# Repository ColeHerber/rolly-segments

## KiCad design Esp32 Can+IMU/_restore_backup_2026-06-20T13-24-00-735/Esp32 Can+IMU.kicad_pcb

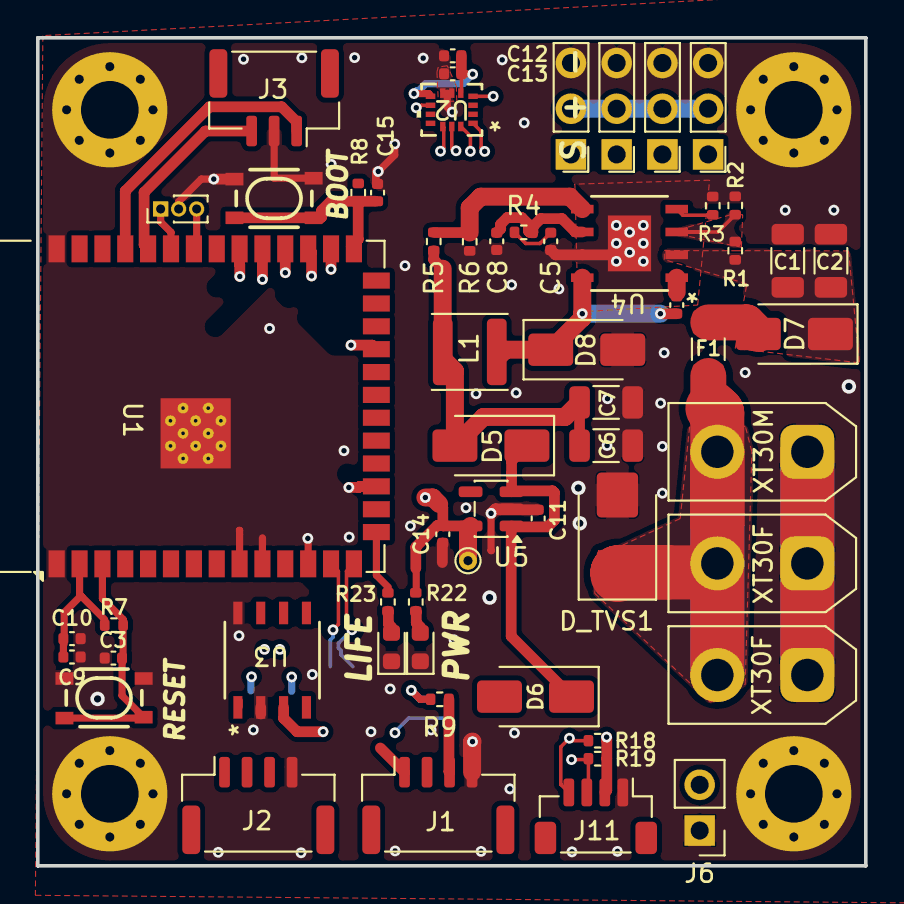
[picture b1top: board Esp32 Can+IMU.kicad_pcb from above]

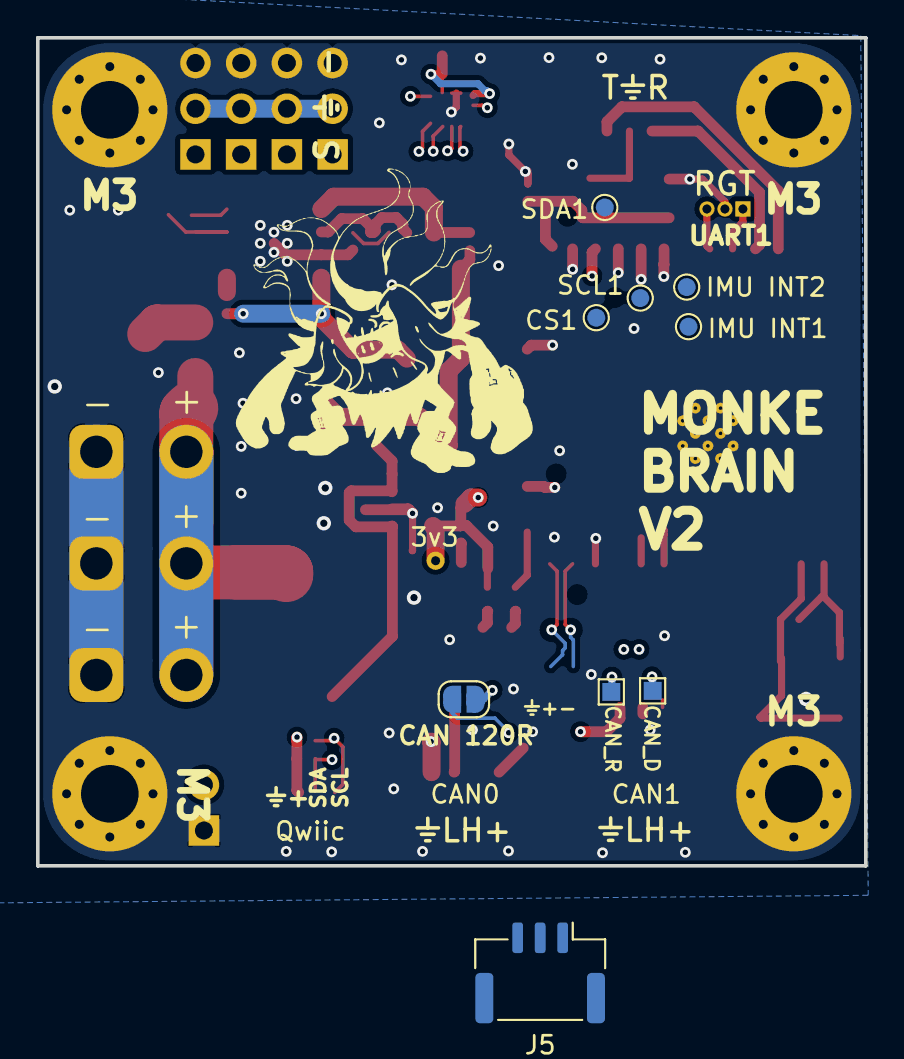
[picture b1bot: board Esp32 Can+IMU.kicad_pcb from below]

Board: 4 copper layers, 46.0 x 46.0 mm, 71 parts (10 on the bottom side), 39 nets.

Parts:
Boot2: BOOT; Push_SMD_4.2x3.2mm
C1, C2: 2.2uF 100v; C_1206_3216Metric
C3, C4, C9, C12, C13, C15: 100nF; C_0402_1005Metric
C5: 6.8nF; C_0402_1005Metric
C6, C7: 47uF 10v; C_1206_3216Metric
C8: 39pF; C_0402_1005Metric
C10: 22uF; C_0402_1005Metric
C11: 1uF 10V X5R; C_0402_1005Metric
C14: 4.7uF 10V X5R; C_0402_1005Metric
CAND1: CAN_D; TestPoint_Pad_1.0x1.0mm
CANR1: CAN_R; TestPoint_Pad_1.0x1.0mm
CAN_TERM1: CAN 120R; SolderJumper-2_P1.3mm_Open_RoundedPad1.0x1.5mm
D3: PWR; LED_0603_1608Metric
D4: LIFE; LED_0603_1608Metric
D5, D6: SS54; D_SMA
D7, D8: SS56; D_SMA
D_TVS1: SMBJ58A; D_SMB
F1: C41367225; Fuse_1206_3216Metric_Pad1.42x1.75mm_HandSolder
H1, H2, H3, H4: M3; MountingHole_3.2mm_M3_Pad_Via
J1: CAN0; JST_GH_SM04B-GHS-TB_1x04-1MP_P1.25mm_Horizontal
J2: CAN1; JST_GH_SM04B-GHS-TB_1x04-1MP_P1.25mm_Horizontal
J3: UART0; JST_GH_SM03B-GHS-TB_1x03-1MP_P1.25mm_Horizontal
J4: UART1; PinHeader_1x03_P1.00mm_Vertical
J5: USB; JST_GH_BM03B-GHS-TBT_1x03-1MP_P1.25mm_Vertical
J6: 5V PWR; PinHeader_1x02_P2.54mm_Vertical
J7: PWM1; PinHeader_1x03_P2.54mm_Vertical_Close
J8: PWM2; PinHeader_1x03_P2.54mm_Vertical_Close
J9: PWM3; PinHeader_1x03_P2.54mm_Vertical_Close
J10: PWM4; PinHeader_1x03_P2.54mm_Vertical_Close
J11: Qwiic; JST_SH_BM04B-SRSS-TB_1x04-1MP_P1.00mm_Vertical
L1: 8.2uH; L_Changjiang_FNR4010S
R1: 523k; R_0402_1005Metric
R2: 84.5kΩ; R_0402_1005Metric
R3: 162kΩ; R_0402_1005Metric
R4: 13.0kΩ; R_0402_1005Metric
R5: 59kΩ; R_0402_1005Metric
R6: 10.2kΩ; R_0402_1005Metric
R7, R8: 10k; R_0402_1005Metric
R9: 120Ω; R_0402_1005Metric
R18, R19: 4.7kΩ; R_0402_1005Metric
R22: 1k; R_0402_1005Metric
R23: 100Ω; R_0402_1005Metric
Reset1: RESET; Push_SMD_4.2x3.2mm
TP_3v3: 3v3; TestPoint_THTPad_D1.0mm_Drill0.5mm
TP_CS1: CS1; TestPoint_Pad_D1.0mm
TP_INT1: IMU INT1; TestPoint_Pad_D1.0mm
TP_INT2: IMU INT2; TestPoint_Pad_D1.0mm
TP_SCL1: SCL1; TestPoint_Pad_D1.0mm
TP_SDA1: SDA1; TestPoint_Pad_D1.0mm
U1: ESP32-S3-WROOM-1
U2: ISM6HG256XTR; LGA14L_2P5X3_STM
U3: SN65HVD230DR; D8-L
U4: TPS54360BQDDARQ1; DDA8_3P1X2P4_TEX-L
U5: AP2112K-3.3; SOT-23-5
XT30F1, XT30F2: XT30F; AMASS_XT30UPB-F_1x02_P5.0mm_Vertical
XT30M1: XT30M; AMASS_XT30UPB-M_1x02_P5.0mm_Vertical

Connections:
+3.3V: C9.2, C10.1, C12.2, C13.1, C14.2, J11.2, R7.1, R8.2, R18.1, R19.2, R22.2, TP_3v3.1 (1_1), U1.2 (3V3), U2.5 (VDDIO), U2.8 (VDD), U3.3 (VCC), U5.5 (VOUT)
+5V: C11.2, D5.1 (K), D6.1 (K), J6.2, J7.2, J8.2, J9.2, J10.2, U5.1 (VIN), U5.3 (EN)
CAN+: CAN_TERM1.2 (B), J1.2, J2.2, U3.7 (CANH)
CAN-: J1.3, J2.3, R9.2, U3.6 (CANL)
CAN_D: CAND1.1 (1_1), U1.9 (IO16), U3.1 (D)
CAN_R: CANR1.1 (1_1), U1.10 (IO17), U3.4 (R)
CS: TP_CS1.1 (1_1), U1.23 (IO21), U2.12 (CS)
FB: R5.2, R6.1, U4.5 (FB)
GND: Boot2.2, C1.2, C2.2, C3.1, C5.2, C6.2, C7.2, C8.2, C9.1, C10.2, C11.1, C12.1, C13.2, C14.1, C15.1, D3.1 (K), D4.1 (K), D8.2 (A), D_TVS1.2 (A), H1.1 (1_1), H2.1 (1_1), H3.1 (1_1), H4.1 (1_1), J1.4, J2.4, J3.2, J4.2, J5.1, J6.1, J7.3, J8.3, J9.3, J10.3, J11.1, R2.2, R3.2, R6.2, Reset1.1, U1.1 (GND), U1.40 (GND), U1.41 (GND), U2.6 (GND), U2.7 (GND), U3.2 (GND), U3.8 (RS), U4.7 (GND), U4.EPAD, U5.2 (GND), XT30F1.1, XT30F2.1, XT30M1.1
INT1: TP_INT1.1 (1_1), U1.31 (IO38), U2.4 (INT1)
INT2: TP_INT2.1 (1_1), U1.32 (IO39), U2.9 (INT2)
unnamed: C5.1, R4.2
unnamed: CAN_TERM1.1 (A), R9.1
unnamed: D3.2 (A), R22.1
unnamed: D4.2 (A), R23.1
unnamed: C6.1, C7.1, D5.2 (A), L1.2, R5.1
unnamed: D6.2 (A), J1.1, J2.1
unnamed: D7.2 (A), F1.2
unnamed: C4.2, D8.1 (K), L1.1, U4.8 (SW)
unnamed: D_TVS1.1 (K), F1.1, XT30F1.2, XT30F2.2, XT30M1.2
unnamed: C3.2, R7.2, Reset1.2, U1.3 (EN)
unnamed: Boot2.1, C15.2, R8.1, U1.27 (IO0)
unnamed: R23.2, U1.15 (IO3)
unnamed: C4.1, U4.1 (BOOT)
unnamed: C8.1, R4.1, U4.6 (COMP)
unnamed: R1.2, R2.1, U4.3 (EN)
unnamed: R3.1, U4.4 (RT/CLK)
SCL: TP_SCL1.1 (1_1), U1.29 (IO36), U2.13 (SCL)
SCL0: J11.4, R18.2, U1.17 (IO9)
SDA: TP_SDA1.1 (1_1), U1.28 (IO35), U2.14 (SDA)
SDA0: J11.3, R19.1, U1.12 (IO8)
SDO/TA0: U1.30 (IO37), U2.1 (SDO/TA0)
UART0RX: J3.3, U1.36 (RXD0)
UART0TX: J3.1, U1.37 (TXD0)
UART1RX: J4.3, U1.34 (IO41)
UART1TX: J4.1, U1.35 (IO42)
USB_D+: J5.2, U1.14 (USB_D+)
USB_D-: J5.3, U1.13 (USB_D-)
VBUS: C1.1, C2.1, D7.1 (K), R1.1, U4.2 (VIN)

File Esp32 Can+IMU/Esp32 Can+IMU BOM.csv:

"Reference","Qty","Value","Footprint","LCSC#","DNP","Exclude from Board","Exclude from BOM","Datasheet"
"Boot1,R15,R16,R17,Reset1","5","10kΩ","Resistor_SMD:R_0402_1005Metric","","","","",""
"C1,C2","2","2.2uF 100v","Capacitor_SMD:C_1206_3216Metric","","","","",""
"C3,C4,C9,C15","4","100nF","Capacitor_SMD:C_0402_1005Metric","","","","",""
"C5","1","6.8nF","Capacitor_SMD:C_0402_1005Metric","","","","",""
"C6,C7","2","47uF 10v","Capacitor_SMD:C_1206_3216Metric","","","","",""
"C8","1","39pF","Capacitor_SMD:C_0402_1005Metric","","","","",""
"C10","1","22uF","Capacitor_SMD:C_0402_1005Metric","","","","",""
"C11","1","1uF 10V X5R","Capacitor_SMD:C_0402_1005Metric","","","","",""
"C12,C13","2","100nf","Capacitor_SMD:C_0402_1005Metric","","","","",""
"C14","1","4.7uF 10V X5R","Capacitor_SMD:C_0402_1005Metric","","","","",""
"D2,D5,D6","3","SS54","Diode_SMD:D_SMA","","","","",""
"D3","1","Green","LED_SMD:LED_0603_1608Metric","C2986048","","","",""
"D4","1","Red","LED_SMD:LED_0603_1608Metric","C19171390","","","","https://media.digikey.com/pdf/Data%20Sheets/Rohm%20PDFs/SMLE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"
"D7,D8","2","SS56","Diode_SMD:D_SMA","","","","",""
"D_TVS1","1","SMBJ58A","Diode_SMD:D_SMB","","","","",""
"F1","1","C41367225","Fuse:Fuse_1206_3216Metric_Pad1.42x1.75mm_HandSolder","C41367225","","","",""
"J1,J2","2","Conn_01x04_Pin","Connector_JST:JST_GH_SM04B-GHS-TB_1x04-1MP_P1.25mm_Horizontal","C189895","","","",""
"J11","1","Qwiic_Vertical","Connector_JST:JST_SH_BM04B-SRSS-TB_1x04-1MP_P1.00mm_Vertical","C160390","","","","https://www.jst-mfg.com/product/pdf/eng/eSH.pdf"
"J12","1","USB_C_Receptacle_USB2.0_16P","Connector_USB:USB_C_Receptacle_G-Switch_GT-USB-7051x","C2843970","","","","https://www.usb.org/sites/default/files/documents/usb_type-c.zip"
"L1","1","8.2uH","Inductor_SMD:L_Changjiang_FNR4010S","C45958745","","","",""
"R1","1","523k","Resistor_SMD:R_0402_1005Metric","","","","",""
"R2","1","84.5kΩ","Resistor_SMD:R_0402_1005Metric","","","","",""
"R3","1","162kΩ","Resistor_SMD:R_0402_1005Metric","","","","",""
"R4","1","13.0kΩ","Resistor_SMD:R_0402_1005Metric","","","","",""
"R5","1","59kΩ","Resistor_SMD:R_0402_1005Metric","","","","",""
"R6","1","10.2kΩ","Resistor_SMD:R_0402_1005Metric","","","","",""
"R7,R8","2","5.1kΩ","Resistor_SMD:R_0402_1005Metric","","","","",""
"R9","1","120Ω","Resistor_SMD:R_0402_1005Metric","","","","",""
"R12,R13,R14","3","33Ω","Resistor_SMD:R_0402_1005Metric","","","","",""
"R18,R19","2","4.7kΩ","Resistor_SMD:R_0402_1005Metric","","","","",""
"R22","1","1k","Resistor_SMD:R_0402_1005Metric","","","","",""
"R23","1","100Ω","Resistor_SMD:R_0402_1005Metric","","","","",""
"SW1,SW2","2","SMD_4.2x3.2mm_h2.5mm","PCM_SparkFun-Switch:Push_SMD_4.2x3.2mm","C843674","","","","https://www.ckswitches.com/media/3130/ck_rk_datasheet.pdf"
"U1","1","ESP32-S3-WROOM-1","RF_Module:ESP32-S3-WROOM-1","C2913198","","","","https://www.espressif.com/sites/default/files/documentation/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"
"U3","1","SN65HVD230DR","Symbol:D8-L","C30530","","","","https://www.ti.com/lit/gpn/sn65hvd230"
"U4","1","TPS54360BQDDARQ1","Transistor_Power_Module:DDA8_3P1X2P4_TEX-L","C2687968","","","","https://www.ti.com/lit/gpn/tps54360b-q1"
"U5","1","AP2112K-3.3","Package_TO_SOT_SMD:SOT-23-5","C22365427","","","","https://www.diodes.com/assets/Datasheets/AP2112.pdf"
"U6","1","USBLC6-2P6","Package_TO_SOT_SMD:SOT-666","C15999","","","","https://www.st.com/resource/en/datasheet/usblc6-2.pdf"
"XT30F1,XT30F2","2","Conn_01x02","Connector_AMASS:AMASS_XT30UPB-F_1x02_P5.0mm_Vertical","C108769","","","",""
"XT30M1","1","Conn_01x02","Connector_AMASS:AMASS_XT30UPB-M_1x02_P5.0mm_Vertical","C19268026","","","",""
"XT302+2F1,Xt302+2F2","2","Conn_01x04_Pin","","C19268028","DNP","Excluded from board","",""

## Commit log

2025-02-20 Copied Alex's work on remote control of board
2025-02-26 encoders not working
2025-03-01 Added servo test code, two motors position control test.
2025-03-10 This code moves 3/4 servos. Not the 2nd closest to usb tho
2025-03-11 going to try a revert rn
2025-03-12 This moves the motors again! But it does smoke them after a couple seconds.....
2025-03-12 Ok, so we got it to move without exploding! Yay. Output ramp helps a ton!
2025-03-12 This code burnt out a fuse on my battery :). Added other motor ampridge limits, further debugging soon.
2025-03-12 Both working, starting to work on bluetooth.
2025-04-03 Ok, all servos work! I got the control loop to work at the theoretical max for the next motors speeds. Onto mQQQQ next!
2025-04-14 Added so many files, can update over air now.
2025-04-14 Let's go
2025-04-16 Switiching from Mac broker to raspberry pi
2025-04-20 mqtt on rolly works great, finalizing contorl. Split between test and controller rn
2025-04-20 Ok not crashing, but this stuff isn't updating right now
2025-04-20 Ok this might work, need to be back near router to test :)
2025-04-20 this code is broken as hell
2025-04-20 uuhhhhh
2025-04-20 Compltley rewritten code that
2025-04-21 This code can't really control the motor, but it is trying so hard to
2025-04-21 This can only control one at a time.
2025-04-21 Removed pos Pid and setup for two motors
2025-04-21 Ok, this code should(tm) work
2025-04-21 Both Motors work!
2025-04-26 Spam message, reaction time good now!
2025-09-14 Revert "Spam message, reaction time good now!"
    This reverts commit ee1b3814abd0993e281fad3c5d36761d0be8c9d2.
2025-09-14 Sept 14 fixes implimented, code now works mostly. You still have to change names manually.
2025-11-30 right before branch
2025-12-01 Balance bot go brr
2025-12-01 balance bot
2025-12-01 PID just around theta
2025-12-01 Double PID
2025-12-01 Final Double PID
2026-06-18 Replace with Rolly bistable mechanism and ESP32 CAN+IMU project
    Adds Bistable/ (MATLAB simulations, Typst math derivation, figures,
    Mermaid charts) and Esp32 Can+IMU/ (KiCad PCB design, PlatformIO
    firmware, pico_uart_bridge source). Removes previous rolly-segments
    firmware content.
2026-06-18 Remove .history embedded git repo from index
    .history is VS Code Local History; it was accidentally staged as a
    submodule. Now properly gitignored.
2026-06-20 Add ESP32 CAN IMU bring-up firmware
    Add IMU SPI debug diagnostics, OTA/debug PlatformIO environments, and bring-up notes for the ISM330BX CS fault investigation.
2026-06-23 Update ESP32 CAN IMU board revision
2026-06-27 Pre stage before rework for pogo pins
2026-06-28 updated schematic with pogo pads
2026-06-28 hand soldering usbLC6
